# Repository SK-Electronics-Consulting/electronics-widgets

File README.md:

# Electronics Widgets

## Background

This is a collection of small boards and tools for use with electronics.  All the PCBs in here are considered independent projects, but are not complex enough to warrant a separate repo.  

## PCBs

| Name          | Status                  | Description                    |
| ------------  | ----------------------- | ----------- |
| Breadboard Power Supply Adapter | V1 Ordered and in use. | Simple Adapter to bring power to breadboards, including 4-wire. |
| GDS Power Supply Entry Point | V1 Tested and working | A simple power entry point to provide a mechanically secure way to connect power supply cables |
| JLink Adapter | V2 & V3 Tested and working | A simple Jlink to SWD adapter with a few extra features.|
| QWIIC and CAN to Saleae Adapter| V1 Tested and working. V2 ordered | Provides a QWIIC connection point, as well as a CAN PHY IC.  |
| RasPi Power Adapter | V1 Tested and in-use | Simple Adapter for power into Raspberry Pi 40-pin connector. |
| REF33xx Adapter | In progress | A Breadboard adapter for the REF33xx series references. |
| SAO Tree Ormanent | V1 Partially Tested | A tidy way to hang SAO boards as decoration |

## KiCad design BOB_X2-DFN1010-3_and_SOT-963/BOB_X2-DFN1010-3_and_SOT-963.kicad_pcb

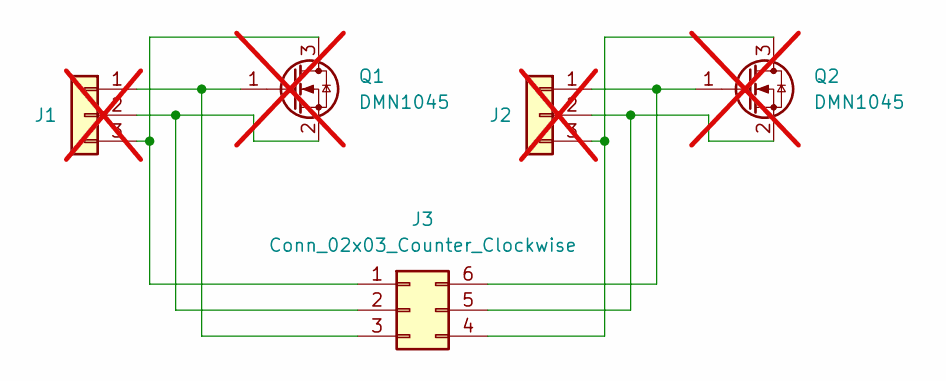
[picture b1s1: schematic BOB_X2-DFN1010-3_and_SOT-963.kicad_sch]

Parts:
J1, J2: Conn_01x03; PinHeader_1x03_P2.54mm_Vertical; not fitted
J3: Conn_02x03_Counter_Clockwise; SOT-963
Q1, Q2: DMN1045; Diodes_X2-DFN1010-3; MPN DMN1045UFR4-7; JLCPCB Part No. C460988; not fitted

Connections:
unnamed: J1.1, J3.3, Q1.1 (G)
unnamed: J1.2, J3.2, Q1.2 (S)
unnamed: J1.3, J3.1, Q1.3 (D)
unnamed: J2.1, J3.6, Q2.1 (G)
unnamed: J2.2, J3.5, Q2.2 (S)
unnamed: J2.3, J3.4, Q2.3 (D)

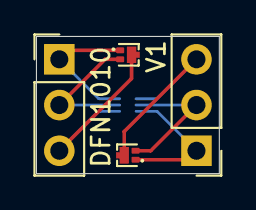
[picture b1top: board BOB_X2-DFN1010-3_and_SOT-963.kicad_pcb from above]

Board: 2 copper layers, 10.2 x 7.6 mm, 5 parts (1 on the bottom side), 6 nets.

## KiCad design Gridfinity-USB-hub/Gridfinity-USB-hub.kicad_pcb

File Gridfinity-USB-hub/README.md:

# Links for Debuggers

* <https://github.com/raspberrypi/debugprobe>  <https://www.raspberrypi.com/products/debug-probe/>  <https://datasheets.raspberrypi.com/debug/raspberry-pi-debug-probe-schematics.pdf>
* pyOCD and openOCD
* <https://sourceforge.net/p/openocd/code/ci/master/tree/tcl/interface/ftdi/swd-resistor-hack.cfg>
* <https://www.nxp.com/design/design-center/software/development-software/mcuxpresso-software-and-tools-/mcu-link-debug-probe:MCU-LINK>
* <https://github.com/probe-rs/rusty-probe>
* <https://github.com/LordsBoards/RoyalBlue54L-Feather-Debugger-Firmware>  <https://github.com/LordsBoards/RoyalBlue54L-Feather-Hardware>
* FT2232

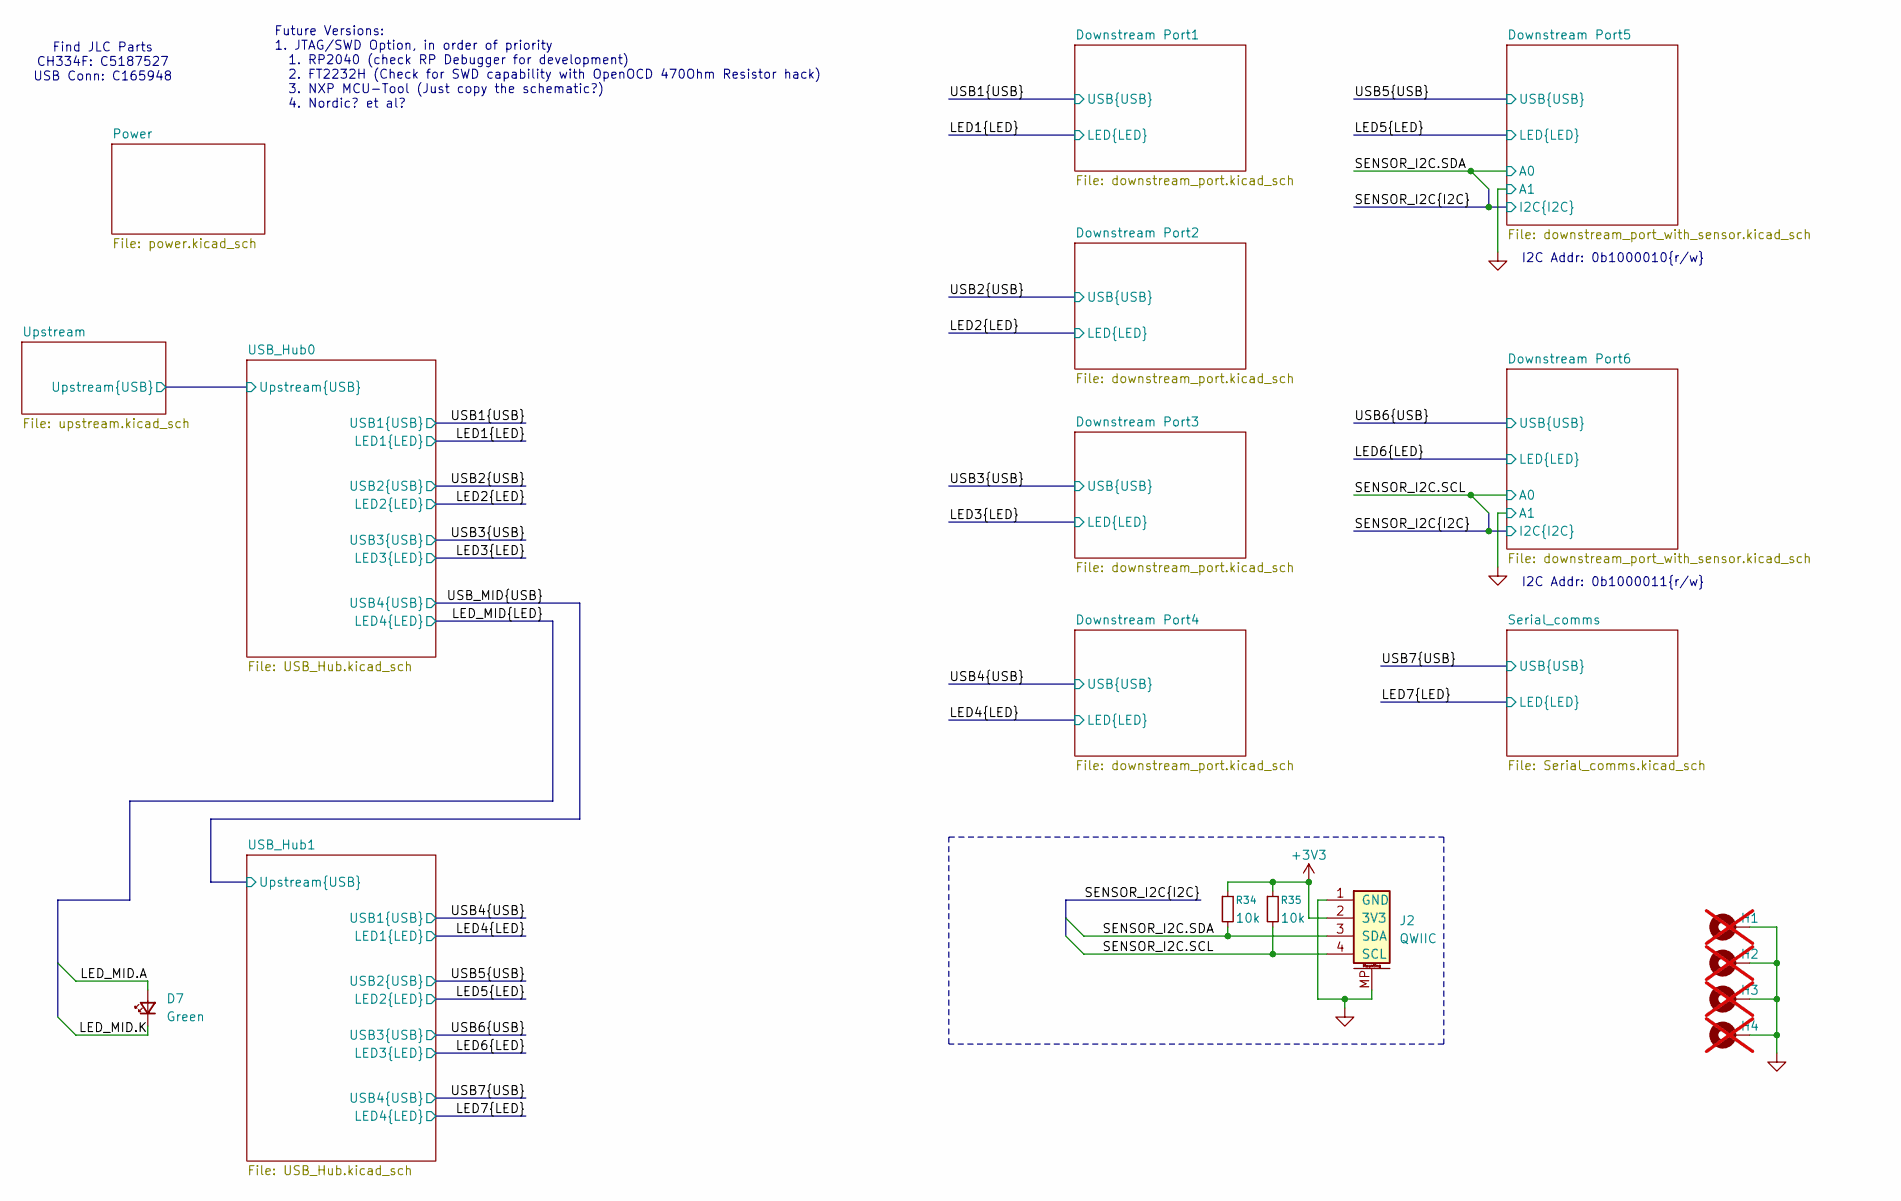
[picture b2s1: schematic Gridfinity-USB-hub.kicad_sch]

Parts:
D7: Green; LED_0402_1005Metric; MPN XL-1005UGC; JLCPCB Part No. C965793
H1, H2, H3, H4: MountingHole_Pad; MountingHole_3.2mm_M3_Pad_Via; not fitted
J2: QWIIC; JST_SH_BM04B-SRSS-TB_1x04-1MP_P1.00mm_Vertical; MPN BM04B-SRSS-TBT(LF)(SN); Digi-Key 455-BM04B-SRSS-TBTCT-ND
R34, R35: 10k; R_0402_1005Metric

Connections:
+3V3: J2.2 (3V3), R34.1, R35.1; also elsewhere on the board
/LED_MID.A: D7.2 (A); also elsewhere on the board
/LED_MID.K: D7.1 (K); also elsewhere on the board
/SENSOR_I2C.SCL: J2.4 (SCL), R35.2; also elsewhere on the board
/SENSOR_I2C.SDA: J2.3 (SDA), R34.2; also elsewhere on the board
GND: H1.1, H2.1, H3.1, H4.1, J2.1 (GND), J2.MP; also elsewhere on the board

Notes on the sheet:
I2C Addr: 0b1000011{r/w}
Find JLC Parts CH334F: C5187527 USB Conn: C165948
Future Versions: 1. JTAG/SWD Option, in order of priority 1. RP2040 (check RP Debugger for development) 2. FT2232H (Check for SWD capability with OpenOCD 470Ohm Resistor hack) 3. NXP MCU-Tool (Just copy the schematic?) 4. Nordic? et al?
I2C Addr: 0b1000010{r/w}

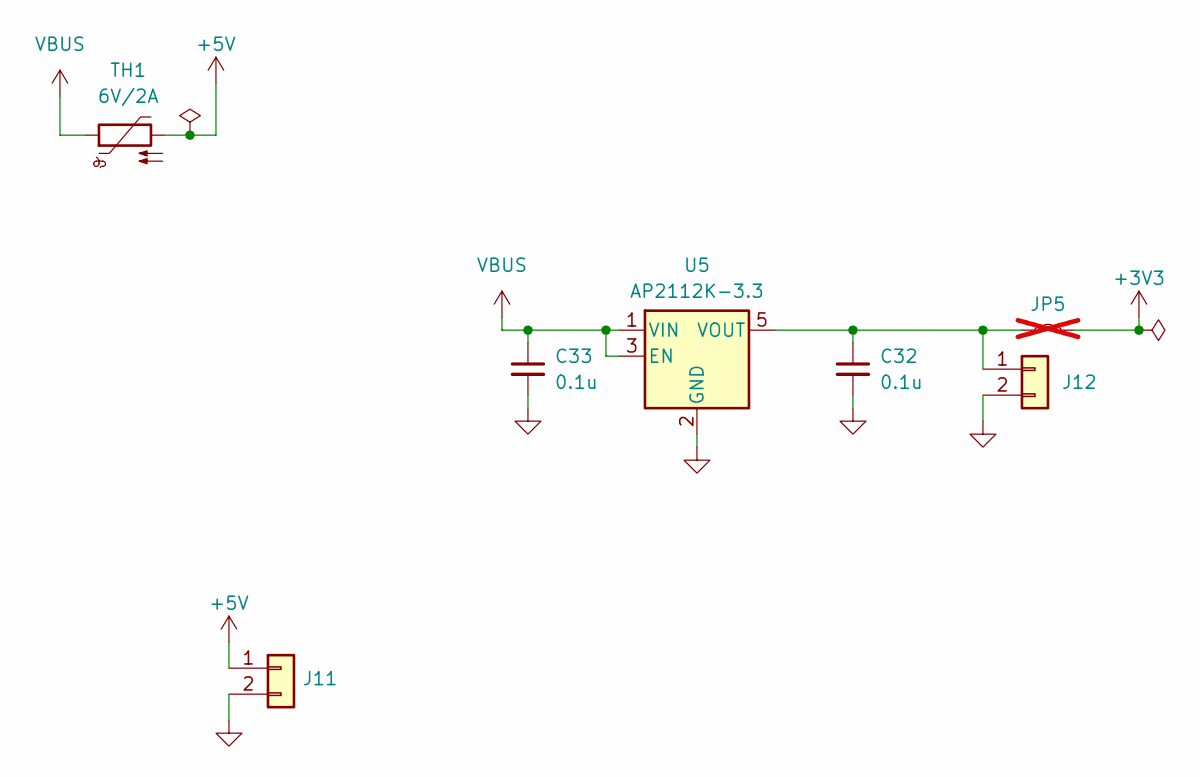
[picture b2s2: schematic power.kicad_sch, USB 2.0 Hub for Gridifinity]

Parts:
C32, C33: 0.1u; C_0402_1005Metric; MPN GRM155R71H104KE14D; JLCPCB Part No. C77020
J11, J12: Conn_01x02; PinSocket_1x02_P2.54mm_Vertical; MPN PZ254V-11-02P; JLCPCB Part No. C492401
JP5: Jumper_2_Small_Bridged; SolderJumper-2_P1.3mm_Bridged2Bar_RoundedPad1.0x1.5mm; not fitted
TH1: 6V/2A; R_0603_1608Metric; JLCPCB Part No. C2757930
U5: AP2112K-3.3; SOT-23-5; MPN AP2112K-3.3TRG1; JLCPCB Part No. C23380830

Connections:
+3V3: JP5.2 (B); also elsewhere on the board
+5V: J11.1, TH1.2; also elsewhere on the board
GND: C32.2, C33.2, J11.2, J12.2, U5.2 (GND); also elsewhere on the board
unnamed: C32.1, J12.1, JP5.1 (A), U5.5 (VOUT)
VBUS: C33.1, TH1.1, U5.1 (VIN), U5.3 (EN); also elsewhere on the board

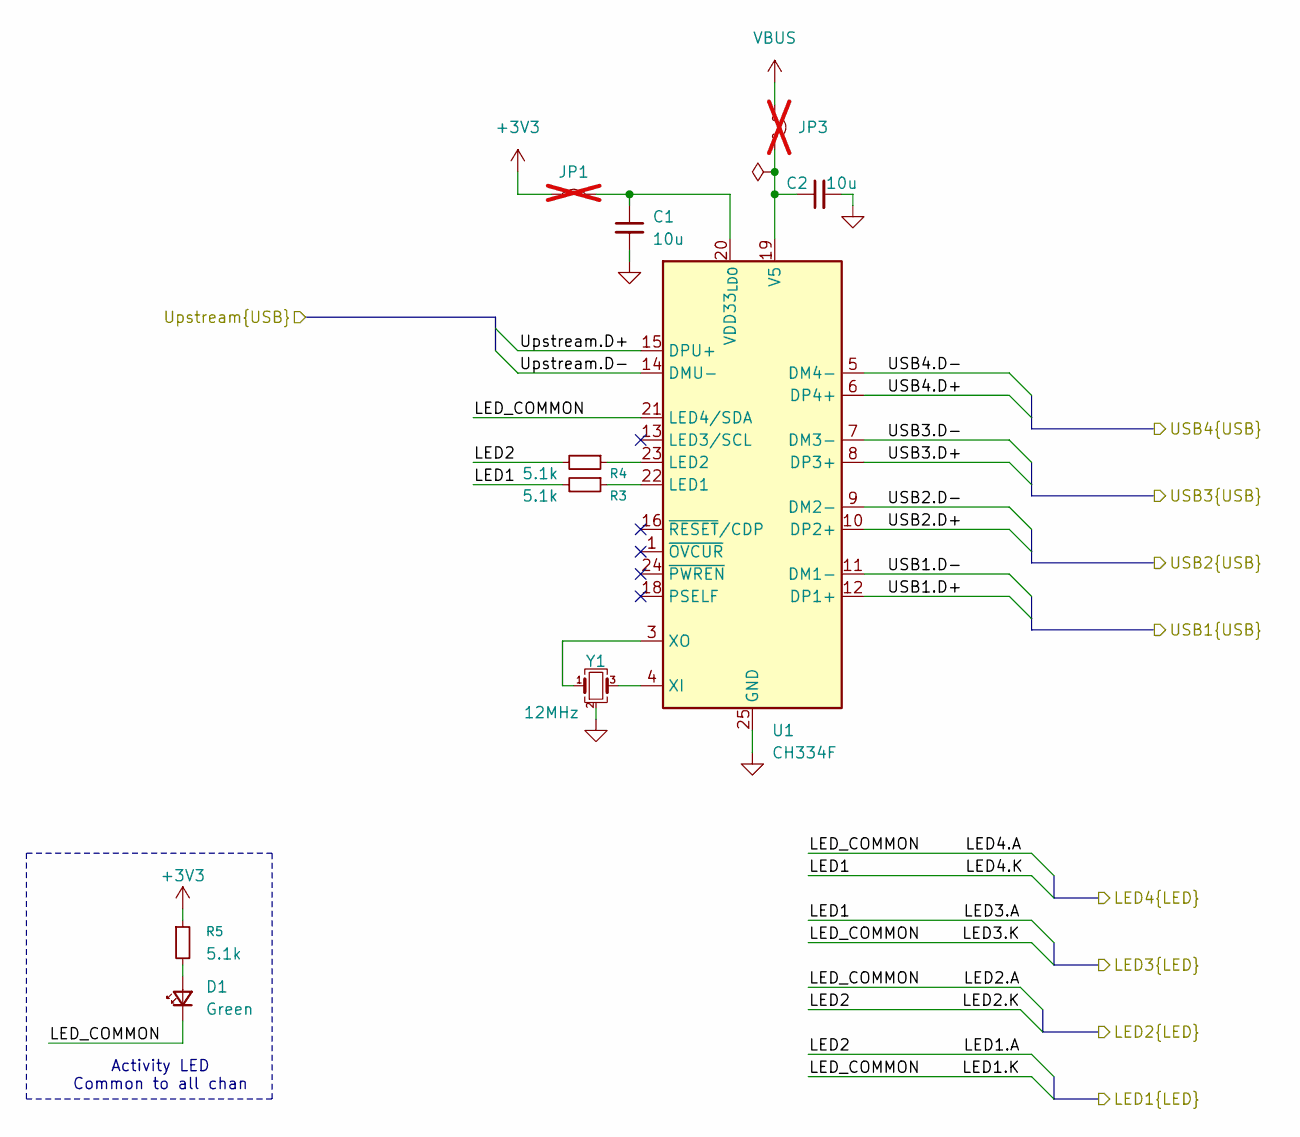
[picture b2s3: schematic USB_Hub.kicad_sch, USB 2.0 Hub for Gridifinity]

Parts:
C1, C2: 10u; C_0603_1608Metric; JLCPCB Part No. C344022
D1: Green; LED_0402_1005Metric; MPN XL-1005UGC; JLCPCB Part No. C965793
JP1: Jumper_2_Small_Bridged; SolderJumper-2_P1.3mm_Bridged2Bar_RoundedPad1.0x1.5mm; not fitted
JP3: Jumper_2_Small_Open; SolderJumper-2_P1.3mm_Open_RoundedPad1.0x1.5mm; not fitted
R3, R4, R5: 5.1k; R_0402_1005Metric; JLCPCB Part No. C25905
U1: CH334F; QFN-24-1EP_4x4mm_P0.5mm_EP2.7x2.7mm; JLCPCB Part No. C5187527
Y1: 12MHz; Crystal_SMD_2520-4Pin_2.5x2.0mm; MPN TXM12M0004252FBCEO00T; JLCPCB Part No. C284155

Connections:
+3V3: JP1.1 (A), R5.1; also elsewhere on the board
/LED2.K: R4.2; also elsewhere on the board
/LED_MID.A: D1.1 (K), U1.21 (LED4/SDA); also elsewhere on the board
/LED_MID.K: R3.2; also elsewhere on the board
/USB1.D+: U1.12 (DP1+); also elsewhere on the board
/USB1.D-: U1.11 (DM1-); also elsewhere on the board
/USB2.D+: U1.10 (DP2+); also elsewhere on the board
/USB2.D-: U1.9 (DM2-); also elsewhere on the board
/USB3.D+: U1.8 (DP3+); also elsewhere on the board
/USB3.D-: U1.7 (DM3-); also elsewhere on the board
/USB_Hub0/Upstream.D+: U1.15 (DPU+); also elsewhere on the board
/USB_Hub0/Upstream.D-: U1.14 (DMU-); also elsewhere on the board
/USB_MID.D+: U1.6 (DP4+); also elsewhere on the board
/USB_MID.D-: U1.5 (DM4-); also elsewhere on the board
GND: C1.2, C2.2, U1.25 (GND), Y1.2 (G), Y1.4 (G); also elsewhere on the board
unnamed: D1.2 (A), R5.2
unnamed: C1.1, JP1.2 (B), U1.20 (VDD33_{LDO})
unnamed: C2.1, JP3.2 (B), U1.19 (V5)
unnamed: R3.1, U1.22 (LED1)
unnamed: R4.1, U1.23 (LED2)
unnamed: U1.4 (XI), Y1.3
unnamed: U1.3 (XO), Y1.1
VBUS: JP3.1 (A); also elsewhere on the board

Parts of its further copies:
C7, C8: 10u; C_0603_1608Metric; JLCPCB Part No. C344022
D6: Green; LED_0402_1005Metric; MPN XL-1005UGC; JLCPCB Part No. C965793
JP2: Jumper_2_Small_Bridged; SolderJumper-2_P1.3mm_Bridged2Bar_RoundedPad1.0x1.5mm; not fitted
JP4: Jumper_2_Small_Open; SolderJumper-2_P1.3mm_Open_RoundedPad1.0x1.5mm; not fitted
R14, R15, R16: 5.1k; R_0402_1005Metric; JLCPCB Part No. C25905
U2: CH334F; QFN-24-1EP_4x4mm_P0.5mm_EP2.7x2.7mm; JLCPCB Part No. C5187527
Y2: 12MHz; Crystal_SMD_2520-4Pin_2.5x2.0mm; MPN TXM12M0004252FBCEO00T; JLCPCB Part No. C284155

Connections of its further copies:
+3V3: JP2.1 (A), R14.1; also elsewhere on the board
/LED4.A: R15.2; also elsewhere on the board
/LED4.K: D6.1 (K), U2.21 (LED4/SDA); also elsewhere on the board
/LED7.K: R16.2; also elsewhere on the board
/USB4.D+: U2.12 (DP1+); also elsewhere on the board
/USB4.D-: U2.11 (DM1-); also elsewhere on the board
/USB5.D+: U2.10 (DP2+); also elsewhere on the board
/USB5.D-: U2.9 (DM2-); also elsewhere on the board
/USB6.D+: U2.8 (DP3+); also elsewhere on the board
/USB6.D-: U2.7 (DM3-); also elsewhere on the board
/USB7.D+: U2.6 (DP4+); also elsewhere on the board
/USB7.D-: U2.5 (DM4-); also elsewhere on the board
/USB_MID.D+: U2.15 (DPU+); also elsewhere on the board
/USB_MID.D-: U2.14 (DMU-); also elsewhere on the board
GND: C7.2, C8.2, U2.25 (GND), Y2.2 (G), Y2.4 (G); also elsewhere on the board
unnamed: D6.2 (A), R14.2
unnamed: C7.1, JP2.2 (B), U2.20 (VDD33_{LDO})
unnamed: C8.1, JP4.2 (B), U2.19 (V5)
unnamed: R16.1, U2.22 (LED1)
unnamed: R15.1, U2.23 (LED2)
unnamed: U2.4 (XI), Y2.3
unnamed: U2.3 (XO), Y2.1
VBUS: JP4.1 (A); also elsewhere on the board

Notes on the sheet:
Activity LED Common to all chan

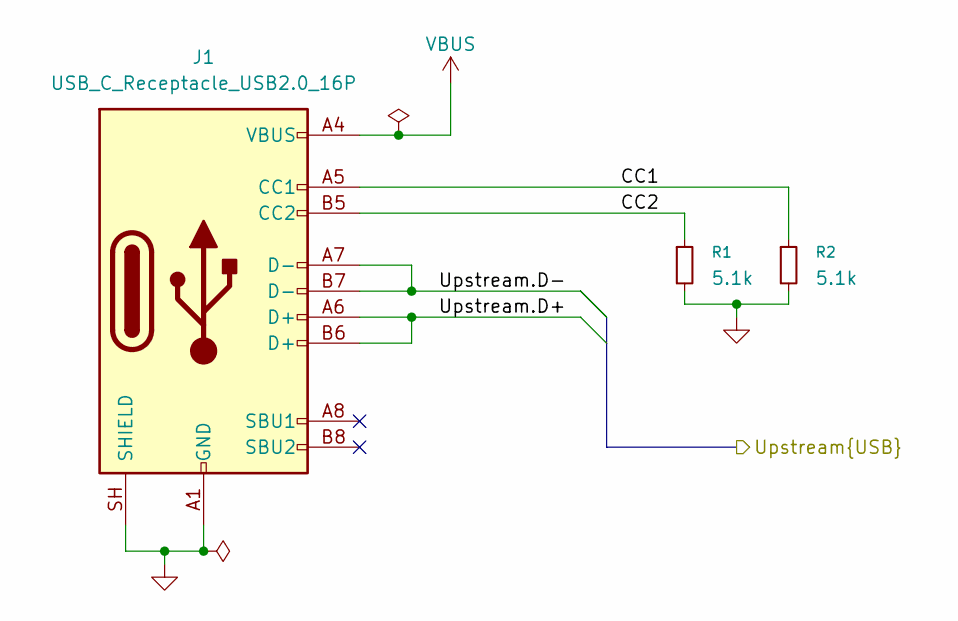
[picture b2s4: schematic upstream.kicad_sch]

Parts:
J1: USB_C_Receptacle_USB2.0_16P; USB_C_Receptacle_G-Switch_GT-USB-7051x; MPN GT-USB-7051A; JLCPCB Part No. C2843970
R1, R2: 5.1k; R_0402_1005Metric; JLCPCB Part No. C25905

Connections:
/USB_Hub0/Upstream.D+: J1.A6 (D+), J1.B6 (D+); also elsewhere on the board
/USB_Hub0/Upstream.D-: J1.A7 (D-), J1.B7 (D-); also elsewhere on the board
/Upstream/CC1: J1.A5 (CC1), R2.1
/Upstream/CC2: J1.B5 (CC2), R1.1
GND: J1.A1 (GND), J1.A12 (GND), J1.B1 (GND), J1.B12 (GND), J1.SH (SHIELD), R1.2, R2.2; also elsewhere on the board
VBUS: J1.A4 (VBUS), J1.A9 (VBUS), J1.B4 (VBUS), J1.B9 (VBUS); also elsewhere on the board

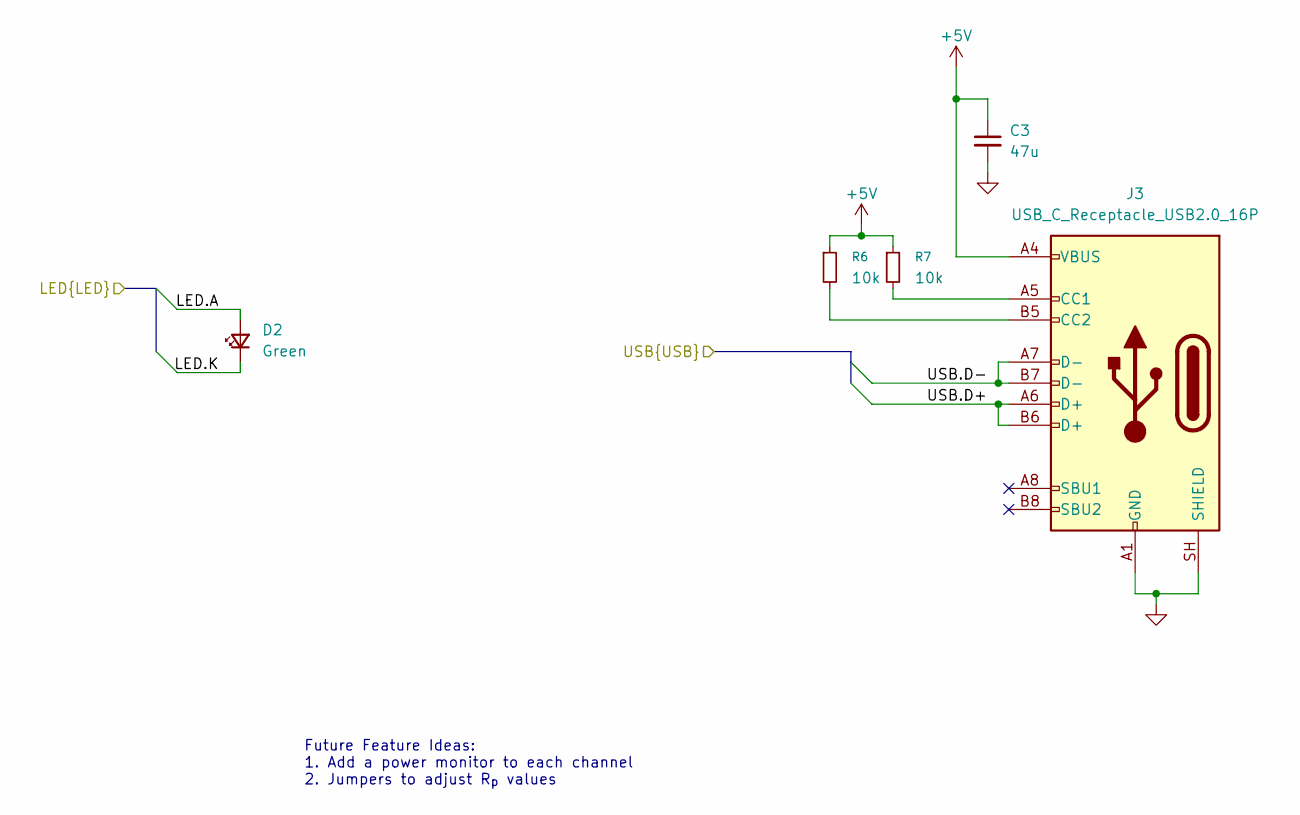
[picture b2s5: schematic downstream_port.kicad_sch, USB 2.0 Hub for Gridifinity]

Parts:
C3: 47u; C_1206_3216Metric; MPN EMK316BBJ476ML-T; JLCPCB Part No. C385907
D2: Green; LED_0402_1005Metric; MPN XL-1005UGC; JLCPCB Part No. C965793
J3: USB_C_Receptacle_USB2.0_16P; USB_C_Receptacle_G-Switch_GT-USB-7051x; MPN GT-USB-7051A; JLCPCB Part No. C2843970
R6, R7: 10k; R_0402_1005Metric; MPN RC0402FR-0710KL; JLCPCB Part No. C60490

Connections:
+5V: C3.1, J3.A4 (VBUS), J3.A9 (VBUS), J3.B4 (VBUS), J3.B9 (VBUS), R6.1, R7.1; also elsewhere on the board
/LED2.K: D2.2 (A); also elsewhere on the board
/LED_MID.A: D2.1 (K); also elsewhere on the board
/USB1.D+: J3.A6 (D+), J3.B6 (D+); also elsewhere on the board
/USB1.D-: J3.A7 (D-), J3.B7 (D-); also elsewhere on the board
GND: C3.2, J3.A1 (GND), J3.A12 (GND), J3.B1 (GND), J3.B12 (GND), J3.SH (SHIELD); also elsewhere on the board
unnamed: J3.A5 (CC1), R7.2
unnamed: J3.B5 (CC2), R6.2

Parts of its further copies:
C4, C5, C6: 47u; C_1206_3216Metric; MPN EMK316BBJ476ML-T; JLCPCB Part No. C385907
D3, D4, D5: Green; LED_0402_1005Metric; MPN XL-1005UGC; JLCPCB Part No. C965793
J4, J5, J6: USB_C_Receptacle_USB2.0_16P; USB_C_Receptacle_G-Switch_GT-USB-7051x; MPN GT-USB-7051A; JLCPCB Part No. C2843970
R8, R9, R10, R11, R12, R13: 10k; R_0402_1005Metric; MPN RC0402FR-0710KL; JLCPCB Part No. C60490

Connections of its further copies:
+5V: C4.1, C5.1, C6.1, J4.A4 (VBUS), J4.A9 (VBUS), J4.B4 (VBUS), J4.B9 (VBUS), J5.A4 (VBUS), J5.A9 (VBUS), J5.B4 (VBUS), J5.B9 (VBUS), J6.A4 (VBUS), J6.A9 (VBUS), J6.B4 (VBUS), J6.B9 (VBUS), R8.1, R9.1, R10.1, R11.1, R12.1, R13.1; also elsewhere on the board
/LED2.K: D3.1 (K); also elsewhere on the board
/LED4.A: D5.2 (A); also elsewhere on the board
/LED4.K: D5.1 (K); also elsewhere on the board
/LED_MID.A: D3.2 (A), D4.1 (K); also elsewhere on the board
/LED_MID.K: D4.2 (A); also elsewhere on the board
/USB2.D+: J4.A6 (D+), J4.B6 (D+); also elsewhere on the board
/USB2.D-: J4.A7 (D-), J4.B7 (D-); also elsewhere on the board
/USB3.D+: J5.A6 (D+), J5.B6 (D+); also elsewhere on the board
/USB3.D-: J5.A7 (D-), J5.B7 (D-); also elsewhere on the board
/USB4.D+: J6.A6 (D+), J6.B6 (D+); also elsewhere on the board
/USB4.D-: J6.A7 (D-), J6.B7 (D-); also elsewhere on the board
GND: C4.2, C5.2, C6.2, J4.A1 (GND), J4.A12 (GND), J4.B1 (GND), J4.B12 (GND), J4.SH (SHIELD), J5.A1 (GND), J5.A12 (GND), J5.B1 (GND), J5.B12 (GND), J5.SH (SHIELD), J6.A1 (GND), J6.A12 (GND), J6.B1 (GND), J6.B12 (GND), J6.SH (SHIELD); also elsewhere on the board
unnamed: J4.A5 (CC1), R9.2
unnamed: J4.B5 (CC2), R8.2
unnamed: J5.A5 (CC1), R11.2
unnamed: J5.B5 (CC2), R10.2
unnamed: J6.A5 (CC1), R13.2
unnamed: J6.B5 (CC2), R12.2

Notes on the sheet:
Future Feature Ideas: 1. Add a power monitor to each channel 2. Jumpers to adjust R_{p} values

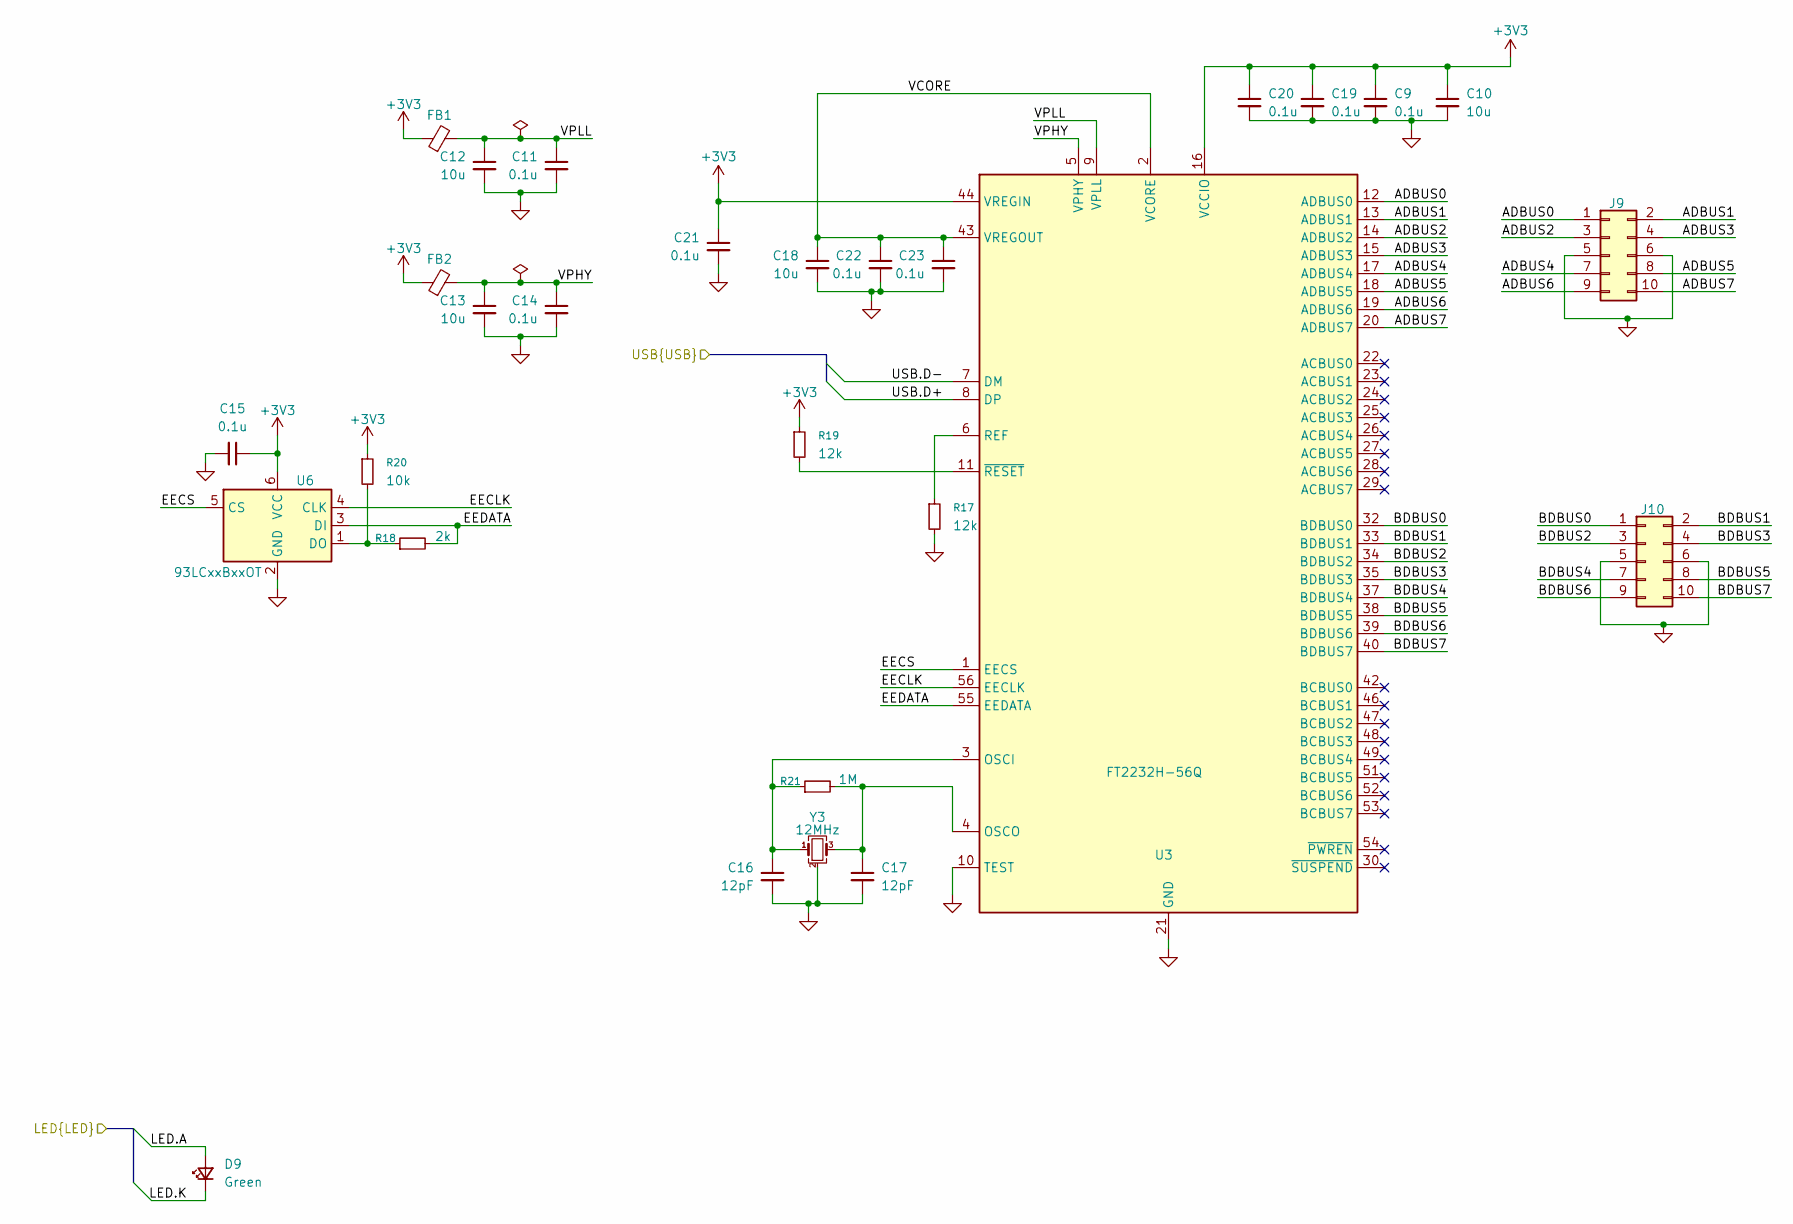
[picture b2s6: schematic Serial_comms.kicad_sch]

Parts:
C9, C11, C14, C15, C19, C20, C21, C22, C23: 0.1u; C_0402_1005Metric
C10, C12, C13, C18: 10u; C_0603_1608Metric; JLCPCB Part No. C344022
C16, C17: 12pF; C_0402_1005Metric
D9: Green; LED_0402_1005Metric; MPN XL-1005UGC; JLCPCB Part No. C965793
FB1, FB2: FerriteBead_Small; L_0402_1005Metric
J9, J10: Conn_02x05_Odd_Even; PinHeader_2x05_P2.54mm_Vertical
R17, R19: 12k; R_0402_1005Metric
R18: 2k; R_0402_1005Metric
R20: 10k; R_0402_1005Metric
R21: 1M; R_0402_1005Metric
U3: FT2232H-56Q; QFN-56-1EP_8x8mm_P0.5mm_EP5.9x5.9mm
U6: 93LCxxBxxOT; SOT-23-6
Y3: 12MHz; Crystal_SMD_2520-4Pin_2.5x2.0mm; MPN TXM12M0004252FBCEO00T; JLCPCB Part No. C284155

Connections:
+3V3: C9.1, C10.1, C15.1, C19.1, C20.1, C21.1, FB1.1, FB2.1, R19.1, R20.1, U3.16 (VCCIO), U3.36 (VCCIO), U3.44 (VREGIN), U3.50 (VCCIO), U6.6 (VCC); also elsewhere on the board
/LED4.K: D9.2 (A); also elsewhere on the board
/LED7.K: D9.1 (K); also elsewhere on the board
/Serial_comms/ADBUS0: J9.1, U3.12 (ADBUS0)
/Serial_comms/ADBUS1: J9.2, U3.13 (ADBUS1)
/Serial_comms/ADBUS2: J9.3, U3.14 (ADBUS2)
/Serial_comms/ADBUS3: J9.4, U3.15 (ADBUS3)
/Serial_comms/ADBUS4: J9.7, U3.17 (ADBUS4)
/Serial_comms/ADBUS5: J9.8, U3.18 (ADBUS5)
/Serial_comms/ADBUS6: J9.9, U3.19 (ADBUS6)
/Serial_comms/ADBUS7: J9.10, U3.20 (ADBUS7)
/Serial_comms/BDBUS0: J10.1, U3.32 (BDBUS0)
/Serial_comms/BDBUS1: J10.2, U3.33 (BDBUS1)
/Serial_comms/BDBUS2: J10.3, U3.34 (BDBUS2)
/Serial_comms/BDBUS3: J10.4, U3.35 (BDBUS3)
/Serial_comms/BDBUS4: J10.7, U3.37 (BDBUS4)
/Serial_comms/BDBUS5: J10.8, U3.38 (BDBUS5)
/Serial_comms/BDBUS6: J10.9, U3.39 (BDBUS6)
/Serial_comms/BDBUS7: J10.10, U3.40 (BDBUS7)
/Serial_comms/EECLK: U3.56 (EECLK), U6.4 (CLK)
/Serial_comms/EECS: U3.1 (EECS), U6.5 (CS)
/Serial_comms/EEDATA: R18.2, U3.55 (EEDATA), U6.3 (DI)
/Serial_comms/VCORE: C18.1, C22.1, C23.1, U3.2 (VCORE), U3.31 (VCORE), U3.43 (VREGOUT)
/Serial_comms/VPHY: C13.1, C14.1, FB2.2, U3.5 (VPHY)
/Serial_comms/VPLL: C11.1, C12.1, FB1.2, U3.9 (VPLL)
/USB7.D+: U3.8 (DP); also elsewhere on the board
/USB7.D-: U3.7 (DM); also elsewhere on the board
GND: C9.2, C10.2, C11.2, C12.2, C13.2, C14.2, C15.2, C16.2, C17.2, C18.2, C19.2, C20.2, C21.2, C22.2, C23.2, J9.5, J9.6, J10.5, J10.6, R17.2, U3.10 (TEST), U3.21 (GND), U3.41 (GND), U3.45 (GND), U3.57 (GND), U6.2 (GND), Y3.2 (G), Y3.4 (G); also elsewhere on the board
unnamed: C16.1, R21.1, U3.3 (OSCI), Y3.1
unnamed: C17.1, R21.2, U3.4 (OSCO), Y3.3
unnamed: R17.1, U3.6 (REF)
unnamed: R19.2, U3.11 (~RESET)
unnamed: R18.1, R20.2, U6.1 (DO)

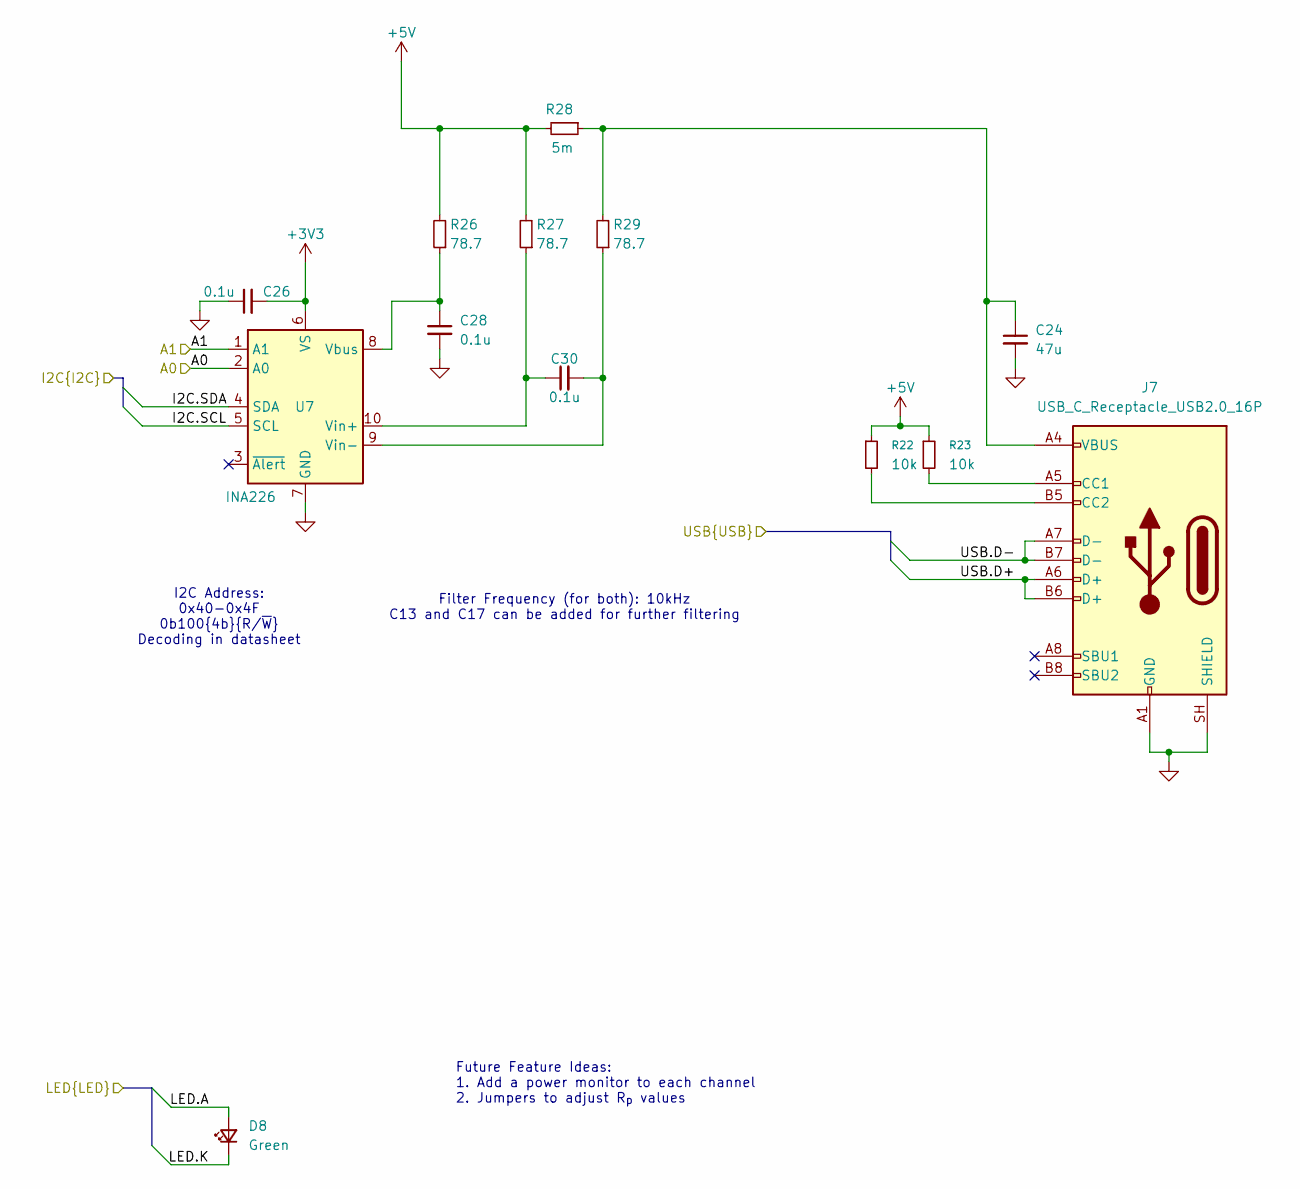
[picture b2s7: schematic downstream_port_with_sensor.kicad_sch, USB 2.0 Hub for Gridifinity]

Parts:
C24: 47u; C_1206_3216Metric; MPN EMK316BBJ476ML-T; JLCPCB Part No. C385907
C26, C28, C30: 0.1u; C_0402_1005Metric; MPN GRM155R71H104KE14D; JLCPCB Part No. C77020
D8: Green; LED_0402_1005Metric; MPN XL-1005UGC; JLCPCB Part No. C965793
J7: USB_C_Receptacle_USB2.0_16P; USB_C_Receptacle_G-Switch_GT-USB-7051x; MPN GT-USB-7051A; JLCPCB Part No. C2843970
R22, R23: 10k; R_0402_1005Metric; MPN RC0402FR-0710KL; JLCPCB Part No. C60490
R26, R27, R29: 78.7; R_0402_1005Metric; MPN AC0402FR-0778R7L; JLCPCB Part No. C227228
R28: 5m; R_1206_3216Metric; MPN HoLLR1206-1W-5mR-1%; JLCPCB Part No. C2988648
U7: INA226; TSSOP-10_3x3mm_P0.5mm; MPN INA226AIDGSR; JLCPCB Part No. C49851

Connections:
+3V3: C26.2, U7.6 (VS); also elsewhere on the board
+5V: R22.1, R23.1, R26.2, R27.2, R28.2; also elsewhere on the board
/LED4.A: D8.1 (K); also elsewhere on the board
/LED4.K: D8.2 (A); also elsewhere on the board
/SENSOR_I2C.SCL: U7.5 (SCL); also elsewhere on the board
/SENSOR_I2C.SDA: U7.2 (A0), U7.4 (SDA); also elsewhere on the board
/USB5.D+: J7.A6 (D+), J7.B6 (D+); also elsewhere on the board
/USB5.D-: J7.A7 (D-), J7.B7 (D-); also elsewhere on the board
GND: C24.2, C26.1, C28.2, J7.A1 (GND), J7.A12 (GND), J7.B1 (GND), J7.B12 (GND), J7.SH (SHIELD), U7.1 (A1), U7.7 (GND); also elsewhere on the board
unnamed: C24.1, J7.A4 (VBUS), J7.A9 (VBUS), J7.B4 (VBUS), J7.B9 (VBUS), R28.1, R29.2
unnamed: J7.A5 (CC1), R23.2
unnamed: J7.B5 (CC2), R22.2
unnamed: C28.1, R26.1, U7.8 (Vbus)
unnamed: C30.1, R27.1, U7.10 (Vin+)
unnamed: C30.2, R29.1, U7.9 (Vin-)

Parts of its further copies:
C25, C27, C29: 0.1u; C_0402_1005Metric; MPN GRM155R71H104KE14D; JLCPCB Part No. C77020
C31: 47u; C_1206_3216Metric; MPN EMK316BBJ476ML-T; JLCPCB Part No. C385907
D10: Green; LED_0402_1005Metric; MPN XL-1005UGC; JLCPCB Part No. C965793
J8: USB_C_Receptacle_USB2.0_16P; USB_C_Receptacle_G-Switch_GT-USB-7051x; MPN GT-USB-7051A; JLCPCB Part No. C2843970
R24, R25, R31: 78.7; R_0402_1005Metric; MPN AC0402FR-0778R7L; JLCPCB Part No. C227228
R30: 5m; R_1206_3216Metric; MPN HoLLR1206-1W-5mR-1%; JLCPCB Part No. C2988648
R32, R33: 10k; R_0402_1005Metric; MPN RC0402FR-0710KL; JLCPCB Part No. C60490
U4: INA226; TSSOP-10_3x3mm_P0.5mm; MPN INA226AIDGSR; JLCPCB Part No. C49851

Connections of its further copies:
+3V3: C25.2, U4.6 (VS); also elsewhere on the board
+5V: R24.2, R25.2, R30.2, R32.1, R33.1; also elsewhere on the board
/LED4.K: D10.1 (K); also elsewhere on the board
/LED7.K: D10.2 (A); also elsewhere on the board
/SENSOR_I2C.SCL: U4.2 (A0), U4.5 (SCL); also elsewhere on the board
/SENSOR_I2C.SDA: U4.4 (SDA); also elsewhere on the board
/USB6.D+: J8.A6 (D+), J8.B6 (D+); also elsewhere on the board
/USB6.D-: J8.A7 (D-), J8.B7 (D-); also elsewhere on the board
GND: C25.1, C27.2, C31.2, J8.A1 (GND), J8.A12 (GND), J8.B1 (GND), J8.B12 (GND), J8.SH (SHIELD), U4.1 (A1), U4.7 (GND); also elsewhere on the board
unnamed: C31.1, J8.A4 (VBUS), J8.A9 (VBUS), J8.B4 (VBUS), J8.B9 (VBUS), R30.1, R31.2
unnamed: J8.A5 (CC1), R33.2
unnamed: J8.B5 (CC2), R32.2
unnamed: C27.1, R24.1, U4.8 (Vbus)
unnamed: C29.1, R25.1, U4.10 (Vin+)
unnamed: C29.2, R31.1, U4.9 (Vin-)

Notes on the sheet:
Future Feature Ideas: 1. Add a power monitor to each channel 2. Jumpers to adjust R_{p} values
Filter Frequency (for both): 10kHz C13 and C17 can be added for further filtering
I2C Address: 0x40-0x4F 0b100{4b}{R/~{W}} Decoding in datasheet

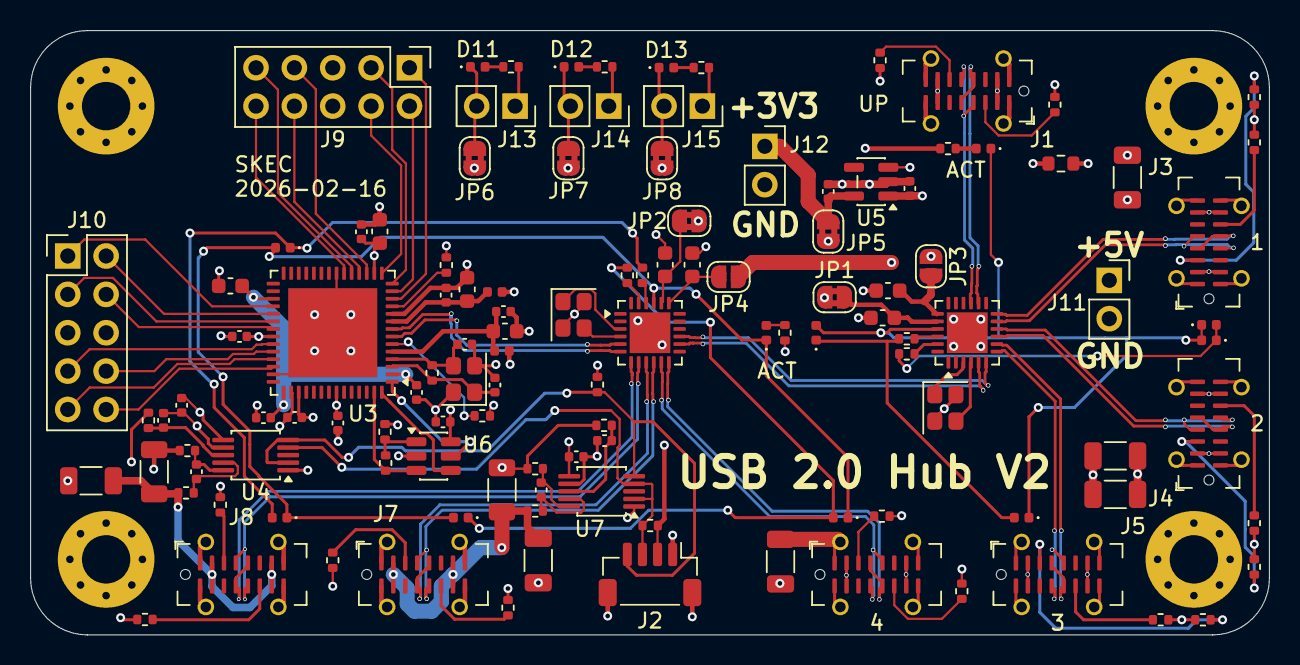
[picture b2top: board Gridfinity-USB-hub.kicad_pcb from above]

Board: 4 copper layers, 82.0 x 40.0 mm, 124 parts (0 on the bottom side), 103 nets.

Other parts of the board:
D11, D12, D13: Green; LED_0402_1005Metric
J13, J14, J15: Conn_01x02; PinSocket_1x02_P2.54mm_Vertical
JP6, JP7, JP8: Jumper_2_Small_Bridged; SolderJumper-2_P1.3mm_Bridged2Bar_RoundedPad1.0x1.5mm
R36, R37, R38: 2k; R_0402_1005Metric

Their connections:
GND: JP6.2 (B), JP7.2 (B), JP8.2 (B); also elsewhere on the board
unnamed: D11.2 (A), R36.1
unnamed: D11.1 (K), J13.2, JP6.1 (A)
unnamed: D12.2 (A), R37.1
unnamed: D12.1 (K), J14.2, JP7.1 (A)
unnamed: D13.2 (A), R38.1
unnamed: D13.1 (K), J15.2, JP8.1 (A)
unnamed: J13.1, R36.2
unnamed: J14.1, R37.2
unnamed: J15.1, R38.2
